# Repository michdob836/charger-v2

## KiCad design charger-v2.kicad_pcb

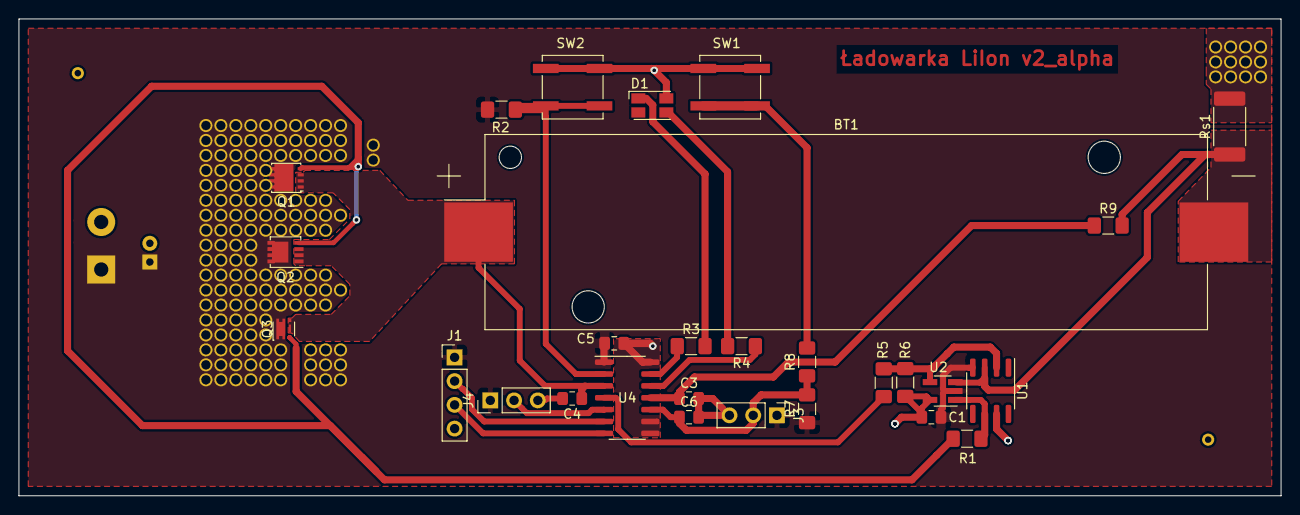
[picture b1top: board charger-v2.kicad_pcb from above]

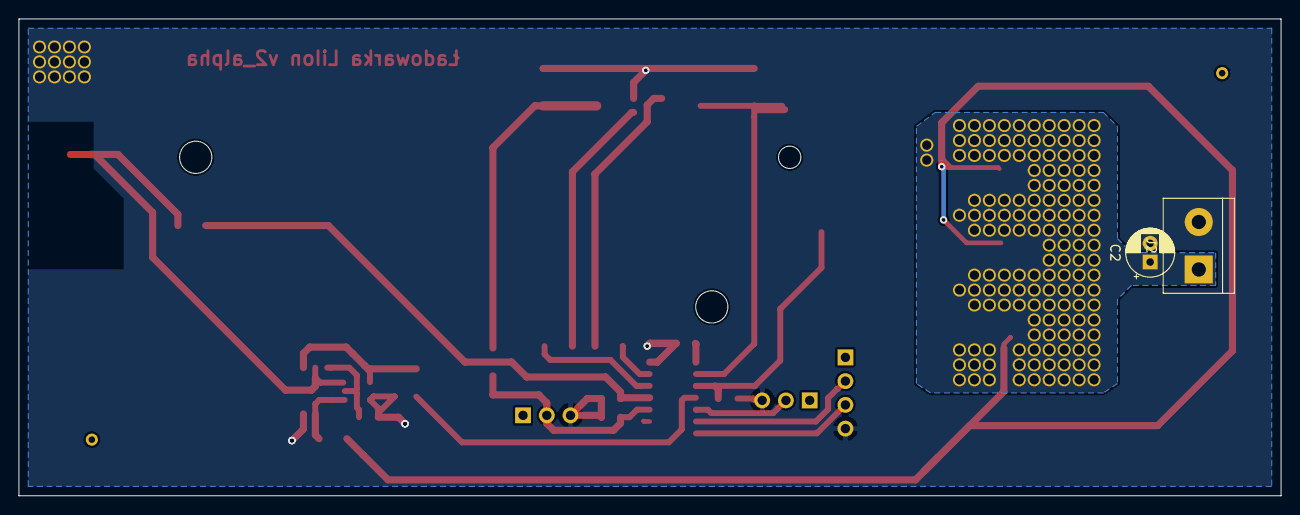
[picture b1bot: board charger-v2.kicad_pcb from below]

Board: 2 copper layers, 135.0 x 51.0 mm, 30 parts (2 on the bottom side), 18 nets.

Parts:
BT1: Battery_Cell; BatteryHolder_Keystone_1042_1x18650
C1, C5, C6: 100n; C_0805_2012Metric_Pad1.15x1.40mm_HandSolder
C2: 100u; CP_Radial_D5.0mm_P2.00mm
C3, C4: 10n; C_0805_2012Metric_Pad1.15x1.40mm_HandSolder
D1: LED_Dual_ACA; LED_Avago_PLCC4_3.2x2.8mm_CW
J1: Conn_01x06_Male; PinHeader_1x04_P2.54mm_Vertical
J2: Screw_Terminal_01x02; TerminalBlock_bornier-2_P5.08mm
J3, J4: Conn_01x03_Male; PinHeader_1x03_P2.54mm_Vertical
Q1: AON7407; DFN-8-1EP_3x3mm_P0.65mm_EP1.55x2.4mm
Q2: SI7615CDN-T1-GE3 d.n.p.; Vishay_PowerPAK_1212-8_Single
Q3: SIA427DJ-T1-GE3 d.n.p.; Vishay_PowerPAK_SC70-6L_Single
R1: 20R; R_1206_3216Metric_Pad1.42x1.75mm_HandSolder
R2, R7: 4k7; R_1206_3216Metric_Pad1.42x1.75mm_HandSolder
R3, R4, R8: 330R; R_1206_3216Metric_Pad1.42x1.75mm_HandSolder
R5: 9k; R_1206_3216Metric_Pad1.42x1.75mm_HandSolder
R6, R9: 1k; R_1206_3216Metric_Pad1.42x1.75mm_HandSolder
Rs1: 83m 0.5%; R_2512_6332Metric_Pad1.52x3.35mm_HandSolder
SW1: RESET; SW_SPST_B3SL-1002P
SW2: HW_BUTTON; SW_SPST_B3SL-1002P
U1: AD8551; SOIC-8_3.9x4.9mm_P1.27mm
U2: alt opamp - dnp; SOT-23-5_HandSoldering
U4: ATtiny414-SS; SOIC-14_3.9x8.7mm_P1.27mm

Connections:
+5V: C1.1, C2.1, C5.1, J1.1, J2.1, J3.1, J4.1, Q1.3, Q2.3, Q3.3, R2.1, R7.1, U1.4, U2.2, U4.1
GND: C1.2, C2.2, C3.2, C4.2, C5.2, C6.2, D1.2, J1.4, J2.2, J3.3, J4.3, R6.2, Rs1.2, SW1.2, SW2.2, U1.7, U2.5, U4.8, U4.9, U4.14
unnamed: BT1.2, R9.2, Rs1.1, U1.3, U2.3
unnamed: D1.1, R4.2
unnamed: Q1.2, Q2.2, Q3.2, R1.1
unnamed: R1.2, U1.6, U2.1
unnamed: R2.2, SW2.1, U4.2
unnamed: R5.2, R6.1, U1.2, U2.4
unnamed: R8.2, SW1.1
RxD: J1.2, U4.6
TxD: J1.3, U4.7
UPDI: C6.1, J3.2, R7.2, R8.1, U4.10
adc_sense1: C3.1, R9.1, U4.11
adc_sense2: BT1.1, C4.1, Q1.1, Q2.1, Q3.1, U4.3
adc_temp: J4.2, U4.5
dac_out: R5.1, U4.4
led1: R3.1, U4.13
led2: R4.1, U4.12

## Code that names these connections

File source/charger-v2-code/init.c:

void init(){
	// analog out:
	// PA6 as DAC_OUT
	VREF.CTRLA |= VREF_DAC0REFSEL_2V5_gc;
	VREF.CTRLA |= VREF_DAC0REFEN_bm;
	_delay_us(25);
	PORTA.PIN6CTRL &= ~PORT_ISC_gm;
	PORTA.PIN6CTRL |= PORT_ISC_INPUT_DISABLE_gc;
	PORTA.PIN6CTRL &= ~PORT_PULLUPEN_bm;
	DAC0.DATA = 0x00; //no current through MOSFET
	DAC0.CTRLA |= DAC_ENABLE_bm;
	DAC0.CTRLA |= DAC_OUTEN_bm;
	
	// digital out:
	// PA3 as LED1
	#define LED1_bp 3
	// PA2 as LED2
	#define LED2_bp 2
	// enable outputs for LEDs
	PORTA.DIR |= 1 << LED1_bp | 1 << LED2_bp;
	// turn them off: 0 -> LED turned on;
	PORTA.OUT |= 1 << LED1_bp | 1 << LED2_bp; 
	
	// digital in:
	// PA4 as HW_BUTTON
	#define HW_BUTTON_bp 4
	PORTA.DIRCLR = 1 << HW_BUTTON_bp;
	// enable inverted input (0 shows as 1 in PORTA.IN)
	PORTA.PIN4CTRL |= PORT_INVEN_bm; 
	
	// analog in:
	// PA1 as ADC_SENSE1
	// PA5 as ADC_SENSE2
	// PA7 as ADC_TEMP
	// disable input buffers of ADC pins
	PORTA.PIN1CTRL = (PORTA.PIN1CTRL & 0xf8) | 0x04;
	PORTA.PIN5CTRL = (PORTA.PIN5CTRL & 0xf8) | 0x04;
	PORTA.PIN7CTRL = (PORTA.PIN7CTRL & 0xf8) | 0x04;
	ADC0.CTRLA |= ADC_RESSEL_10BIT_gc;
	//no samples accumulated
	ADC0.CTRLB  = (ADC0.CTRLB & 0xf8) | 0x00;
	//set volt ref to internal
	ADC0.CTRLC = (ADC0.CTRLC & 0x3f) | 0x1 << 4;
	//configure VREF 
	VREF.CTRLA |= VREF_ADC0REFSEL_4V34_gc;
	VREF.CTRLA |=  VREF_ADC0REFEN_bm;
	//set Sample Capacitance to reduced (recommended for >1V)
	ADC0.CTRLC |= ADC_SAMPCAP_bm;
	// TODO: set pright prescaler ***********************************************
	ADC0.CTRLC = (ADC0.CTRLC & 0xf8) | 0x0 << 0; //temporary to DIV2
	// configure default input for ADC as PIN5 (will measure cell voltage at 0 current)
	ADC0.MUXPOS = (ADC0.MUXPOS & 0xe0) | 0x05;
	// enable ADC
	ADC0.CTRLA |= ADC_ENABLE_bm;
	

		
	// periodic interrupt timer
	RTC.CLKSEL = RTC_CLKSEL_INT1K_gc;
	RTC.DBGCTRL |= RTC_DBGRUN_bm;
	RTC.PITINTCTRL |= RTC_PI_bm; //enable interrupt
	RTC.PITCTRLA |= RTC_PERIOD_CYC128_gc //8Hz @ 1khz int clk
	RTC.PITCTRLA |= RTC_PITEN_bm;
	
		
	return;
}

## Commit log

2019-12-02 little bit of cleanup
2019-12-02 fix .gitignore
2019-12-03 Added uc init
2019-12-03 some code work
2019-12-03 added tex thesis template
2019-12-03 fix mail
2020-01-11 snapshot as of 11.10.20
2020-01-11 add bits of floating around code required for buiding
2020-01-11 add project used for testing stuff
2020-01-13 dodano zapisywanie danych i logi histeryczne.
2020-01-13 zamieniono symlinki na katalogi :)
2020-01-15 hil cleanup and snapshot as of 15.01.20
2020-01-17 snapshot z 17.01.20
2020-01-17 (hopefully) final cleanup
2020-01-17 może taki kod na uc? ('K')
2020-01-18 wreszcie
2020-01-20 final
